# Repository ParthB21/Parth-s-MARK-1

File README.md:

# Parth-s-MARK-1

## Edit: this repository has been edited after feedback to include the BOM in CSV format and a Top case.

This is my first hackpad. It includes 4 switches, 1 rotary encoder and 1 OLED Display. The main MCU is Seeed XIAO RP2040. I would like to thank ScottoKeebs for providing some of the symbols and footprints.
<br> <br><br>
Descriptions of folders in this repository:
<br>
CAD: Includes top and bottom parts in separate for 3D printing. Includes the assembled file to check dimensions.
<br>
PCB: Includes the KiCad files
<br>
Firmware: Includes the firmware

<br>

<br>
This is a screenshot of the schematic
<br>

<br>
This is a screenshot of the PCB
<br>

<br>

<br>

<br>
Screenshots of the bottom case (blue)
<br>
<br>

<br>
Screenshot of the top case (orange)
<br>
<br>

<br>

<br>
Screenshots of assembled Case and PCB
<br>
<br>
<br>

Note: The colors in the images are for easier differentiation between the top and the bottom case and are not the actual colous of the 3D printed parts.
<br>

I used KiCad for the PCB design, OnShape for the CAD design and VSCode for the KMK firmware.
<br>

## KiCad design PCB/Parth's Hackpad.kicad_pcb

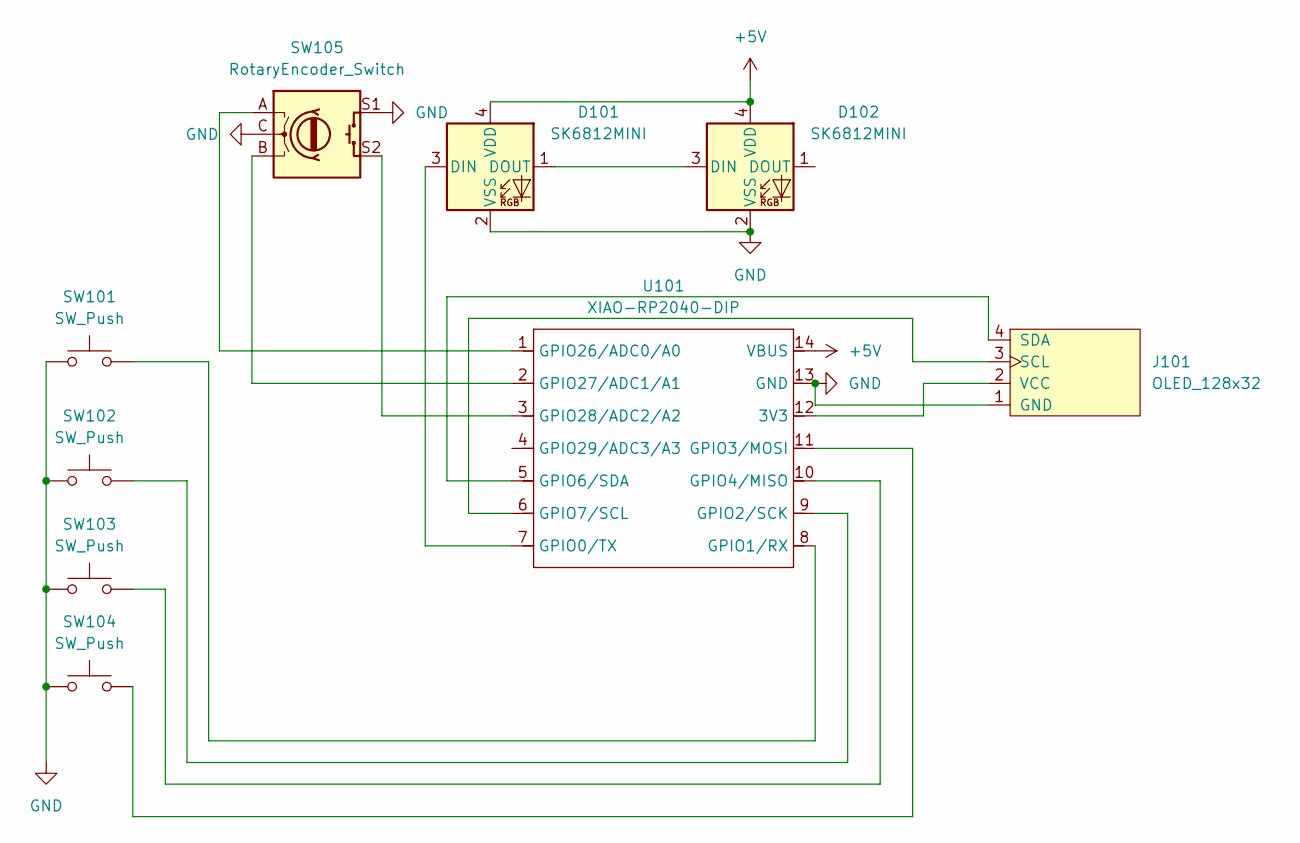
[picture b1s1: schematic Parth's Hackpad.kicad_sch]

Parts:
D101, D102: SK6812MINI; LED_SK6812MINI_PLCC4_3.5x3.5mm_P1.75mm
J101: OLED_128x32
SW101, SW102, SW103, SW104: SW_Push; SW_Cherry_MX_1.00u_PCB
SW105: RotaryEncoder_Switch; RotaryEncoder_Alps_EC11E-Switch_Vertical_H20mm
U101: XIAO-RP2040-DIP

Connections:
+5V: D101.4 (VDD), D102.4 (VDD), U101.14 (VBUS)
GND: D101.2 (VSS), D102.2 (VSS), J101.1 (GND), SW101.1, SW102.1, SW103.1, SW104.1, SW105.C, SW105.S1, U101.13 (GND)
unnamed: D101.3 (DIN), U101.7 (GPIO0/TX)
unnamed: D101.1 (DOUT), D102.3 (DIN)
unnamed: J101.3 (SCL), U101.6 (GPIO7/SCL)
unnamed: J101.4 (SDA), U101.5 (GPIO6/SDA)
unnamed: J101.2 (VCC), U101.12 (3V3)
unnamed: SW101.2, U101.8 (GPIO1/RX)
unnamed: SW102.2, U101.9 (GPIO2/SCK)
unnamed: SW104.2, U101.11 (GPIO3/MOSI)
unnamed: SW103.2, U101.10 (GPIO4/MISO)
unnamed: SW105.A, U101.1 (GPIO26/ADC0/A0)
unnamed: SW105.B, U101.2 (GPIO27/ADC1/A1)
unnamed: SW105.S2, U101.3 (GPIO28/ADC2/A2)

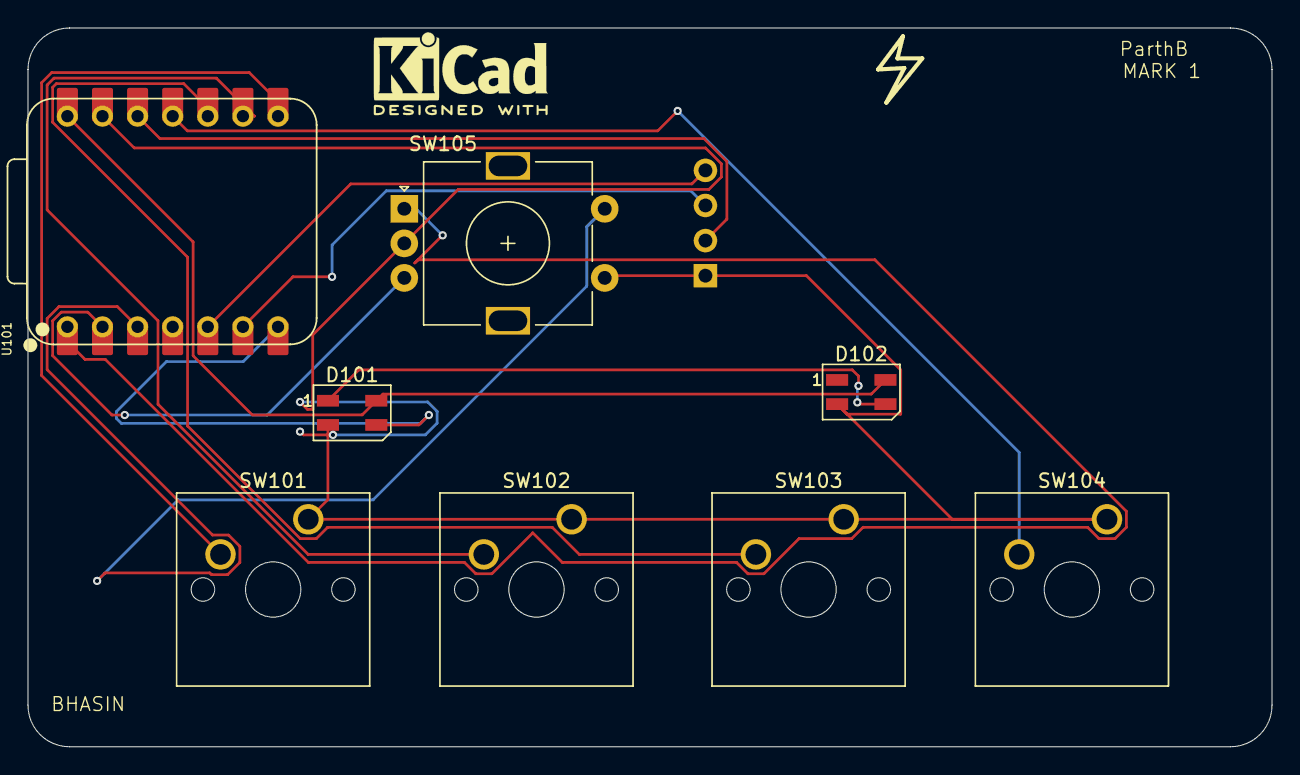
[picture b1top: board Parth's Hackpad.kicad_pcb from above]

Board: 2 copper layers, 90.0 x 52.0 mm, 9 parts (0 on the bottom side), 14 nets.

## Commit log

2025-12-24 Create ReadMe1
2025-12-24 Create Readme2
2025-12-24 Create Readme3
2025-12-24 Add files via upload
    Added case CAD
2025-12-24 Create temp
2025-12-24 Add main.py
2025-12-24 Edited README
    Added detailed project description, images, and BOM.
2025-12-24 Formatted Readme
    Updated the README to improve formatting and clarity.
2025-12-24 Add BOM.csv
2025-12-24 Update BOM.csv to include item details
2025-12-27 Revise image captions and add new screenshots
    Updated figure captions and added new images of the case and PCB.
2025-12-27 Added CAD files
2025-12-27 Update README with folder descriptions
    Added descriptions of folders in the repository.
2025-12-27 Improve formatting in README.md
    Added line breaks for better readability in README.
2025-12-27 Update README
    Added additional information about design tools used.
2025-12-27 Update README
    Added notes about repository edits and clarified case colors.
2025-12-27 Update images in README with new screenshots
